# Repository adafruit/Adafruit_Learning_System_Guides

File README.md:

# Introduction

This is a collection of smaller programs and scripts to display "inline" in [Adafruit Learning System][learn] guides.

Adafruit is an Open Source company. To support Adafruit, please consider buying products at [adafruit.com](https://www.adafruit.com/).

Starting in 2023, guides using a specific Adafruit board will be placed in a subdirectory with that product name to reduce the number of directories under the main directory. If you are creating a new guide, please check if your Adafruit board falls into one of these groups and make your project code directory in the appropriate subfolder.

* Flora/
* ItsyBitsy/
* MagTag/
* MEMENTO/
* NeoTrellis/
* PyLeap/
* PyPortal/
* QTPy/
* Metro/ (all types)
* Matrix_Portal/
* Crickits/
* Gemma/ (both types)

If a new product or project group is contemplated, contact Learn moderators for guidance.

## Issues

Issues with guides should be reported in the guide itself under "Feedback? Corrections?"

## Make Your Own Guides

This repo is only for Adafruit approved Learning System Guides. If you'd like to write your own guide, see [Create your own content with Adafruit Playground!](https://learn.adafruit.com/adafruit-playground-notes).

## Contributing and Testing

For details on contributing for Adafruit approved guides, see the guide [Contribute to the Adafruit Learning System with Git and GitHub](https://learn.adafruit.com/contribute-to-the-adafruit-learning-system-with-git-and-github) and [Contribute to CircuitPython with Git and GitHub](https://learn.adafruit.com/contribute-to-circuitpython-with-git-and-github/github-personal-access-token).

The code here is checked by GitHub Actions against Pylint (for CircuitPython code) or the Arduino compilation process.

Code in directories containing a file called `.circuitpython.skip` will be skipped by Pylint checks.

Code in directories containing a `.[platformname].test` file, such as `.uno.test` will be compiled against the corresponding platform.

[learn]: https://learn.adafruit.com/

## Running pylint locally
Install a specific version of pylint under the name "pylint-learn":
```
pip install pipx
pipx install --suffix=-learn pylint==2.7.1
```
Then use the `pylint_check` script to run pylint on the files or directories
of your choice (note that your terminal *must* be in the top directory of
Adafruit_Learning_System_Guides, not a sub-directory):
```
./pylint_check CircuitPython_Cool_Project
```
## Licensing

Adafruit Learning System code files should have author and license information conforming to the open [SPDX specification](https://www.iso.org/standard/81870.html).
See [this page](https://learn.adafruit.com/contribute-to-the-adafruit-learning-system-with-git-and-github/add-author-and-license-information) for more.

Updated November 18, 2025

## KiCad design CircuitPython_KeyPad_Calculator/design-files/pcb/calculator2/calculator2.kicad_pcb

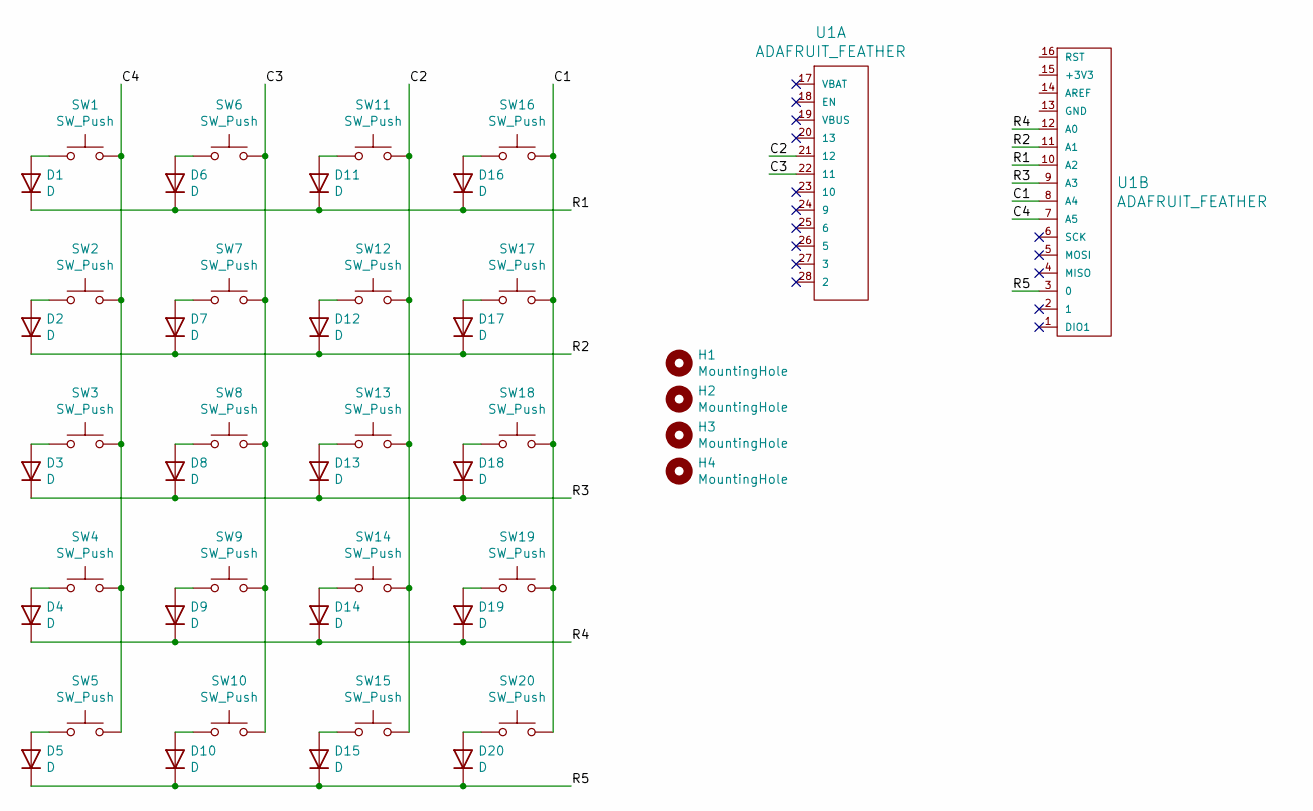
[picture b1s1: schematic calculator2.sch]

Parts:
D1, D2, D3, D4, D5, D6, D7, D8, D9, D10, D11, D12, D13, D14, D15, D16, D17, D18, D19, D20: D; D_DO-41_SOD81_P10.16mm_Horizontal
H1, H2, H3, H4: MountingHole; MountingHole_2.7mm_M2.5
SW1, SW2, SW3, SW4, SW5, SW6, SW7, SW8, SW9, SW10, SW11, SW12, SW13, SW14, SW15, SW16, SW17, SW18, SW19, SW20: SW_Push; SW_Cherry_MX_1.00u_PCB
U1: ADAFRUIT_FEATHER

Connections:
/C1: SW16.2, SW17.2, SW18.2, SW19.2, SW20.2, U1.8 (A4)
/C2: SW11.2, SW12.2, SW13.2, SW14.2, SW15.2, U1.21 (12)
/C3: SW6.2, SW7.2, SW8.2, SW9.2, SW10.2, U1.22 (11)
/C4: SW1.2, SW2.2, SW3.2, SW4.2, SW5.2, U1.7 (A5)
/R1: D1.1 (K), D6.1 (K), D11.1 (K), D16.1 (K), U1.10 (A2)
/R2: D2.1 (K), D7.1 (K), D12.1 (K), D17.1 (K), U1.11 (A1)
/R3: D3.1 (K), D8.1 (K), D13.1 (K), D18.1 (K), U1.9 (A3)
/R4: D4.1 (K), D9.1 (K), D14.1 (K), D19.1 (K), U1.12 (A0)
/R5: D5.1 (K), D10.1 (K), D15.1 (K), D20.1 (K), U1.3 (0)
unnamed: D1.2 (A), SW1.1
unnamed: D2.2 (A), SW2.1
unnamed: D3.2 (A), SW3.1
unnamed: D4.2 (A), SW4.1
unnamed: D5.2 (A), SW5.1
unnamed: D6.2 (A), SW6.1
unnamed: D7.2 (A), SW7.1
unnamed: D8.2 (A), SW8.1
unnamed: D9.2 (A), SW9.1
unnamed: D10.2 (A), SW10.1
unnamed: D11.2 (A), SW11.1
unnamed: D12.2 (A), SW12.1
unnamed: D13.2 (A), SW13.1
unnamed: D14.2 (A), SW14.1
unnamed: D15.2 (A), SW15.1
unnamed: D16.2 (A), SW16.1
unnamed: D17.2 (A), SW17.1
unnamed: D18.2 (A), SW18.1
unnamed: D19.2 (A), SW19.1
unnamed: D20.2 (A), SW20.1

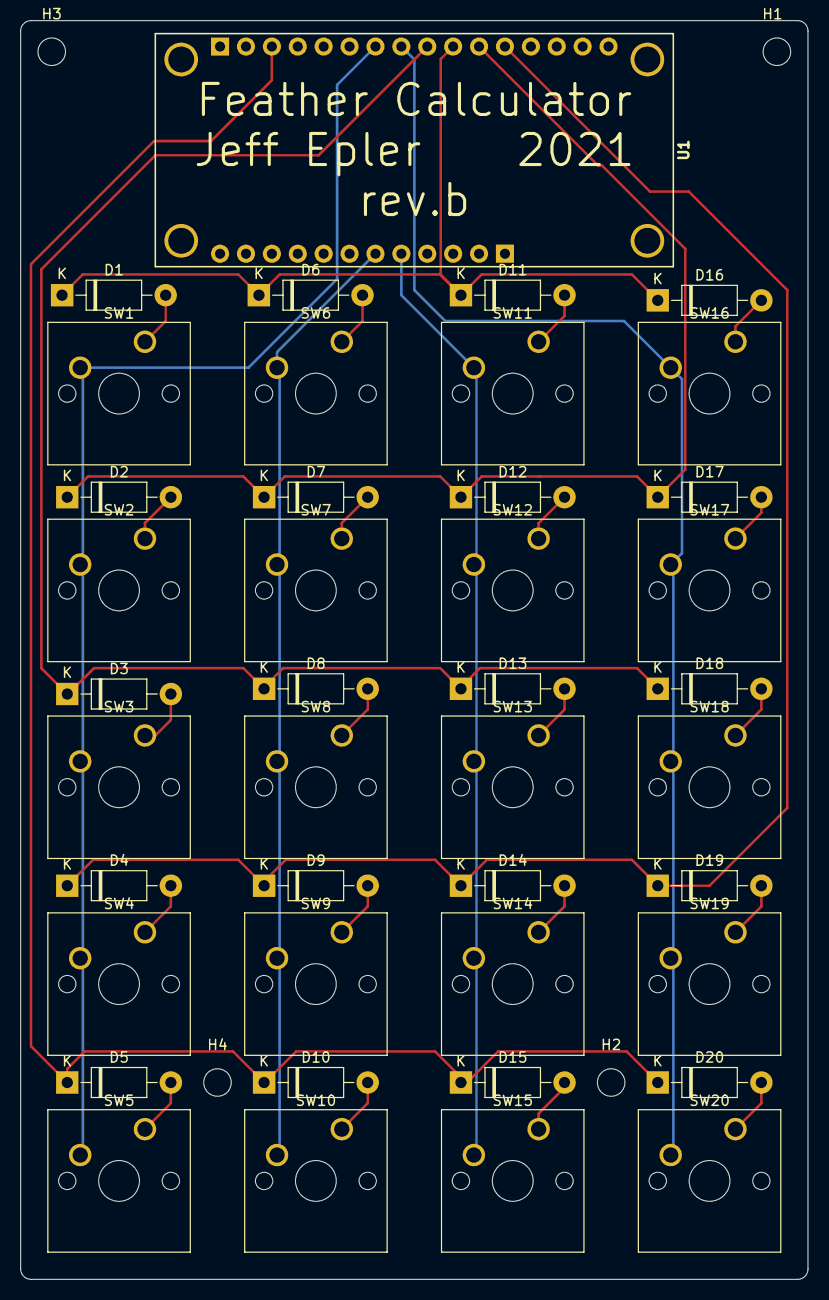
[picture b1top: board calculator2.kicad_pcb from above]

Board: 2 copper layers, 77.2 x 123.4 mm, 45 parts (0 on the bottom side), 29 nets.

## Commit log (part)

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2025-12-09 Format code for consistency in code.py
2025-12-09 Delete NeoPixel_Gemma_Torch directory
    Code moved to https://github.com/adafruit/Adafruit_Learning_System_Guides/tree/main/Gemma/NeoPixel_Gemma_Torch
    Guide updated https://learn.adafruit.com/neopixel-flame-torch/code
2025-12-10 literature clock data files and book info tweak
2025-12-11 fruit jam logo
2025-12-11 png fruit jam logo
2025-12-13 update images
2025-12-15 Clone Introducing Gemma to Gemma/
    For guide changes
2025-12-15 Delete Introducing_Gemma_M0 directory
    Files moved to Gemma/
    Adafruit Introducing Germma M0 updated (1 file, most examples used CircuitPython Essentials examples)
2025-12-17 adding magtag menorah code and bitmap
2025-12-18 Fruit Jam greeting card maker
2025-12-18 add/expand comments about each code file
2025-12-18 add checkbox spritesheet
2026-01-11 CircuitPython Text Editor 2.4" FeatherWing
2026-01-21 Add support for Composite HID devices
2026-01-21 move atexit import up one to make pylint happy
2026-01-21 first commit epaper cam code
2026-01-21 magtag haiku viewer project files
2026-01-22 Update code.py JSON_URL
    There was a change to the folder structure at some point and the MagTag projects were moved inside a MagTag folder and this URL was broken. Corrected to reflect the new URL and tested on my device.
2026-01-22 move haiku loading code, add font file
2026-01-23 Fix Eink bonnet weather station for PIL >= 10
2026-01-26 code and example mp3s
2026-01-26 use PCF font instead of BDF
2026-01-27 update folder name
2026-01-27 adding bass synth code
2026-01-28 take out readonly
    causing problems with stability, filed issue on cp repo
2026-02-10 adding midi breath controller code
2026-02-10 reduced lag in joystick code
2026-02-11 Fix display brightness scaling during fade down
    Adjust brightness scaling for display fade effect, same as fade up, noted in guide feedback
2026-02-13 pylint warning for chip's challenge
2026-02-13 Fruit Jam Tiny Wiki server
2026-02-13 rename storage -> wiki_storage, reduce long lines, change title note on new page, use f-string instead of format, ignore some pylints
2026-02-13 move _escape_html() out of class to normal function.
2026-02-13 fix tiny_wiki typo
2026-02-16 Updating cpb glass lamp code
    Putting the CPB glass lamp code in a directory for learn.
2026-02-17 fixed SPDX error
2026-02-17 Update SPDX license and copyright information
2026-02-20 Disable discovery options in feather_bme280.yaml
    Avoid unauthorised fixed topics like esphome/ping/{device-name}
2026-02-20 adding rpi moonshine voice control neopixels
2026-02-20 add license, code format, add link to original code this was adapted from.
2026-02-21 Replace worldtimeapi.org with time.now/developer API
    Updates 16 files to replace the deprecated worldtimeapi.org time
    service with the new time.now/developer API endpoint.
    ⏺ | Guide | Filename | Change URL |
    |-------|----------|------------|
    | PicoW_YBox3 | PicoW_YBox3.ino |
    `https://time.now/developer/api/timezone/Etc/UTC` |
2026-02-23 fix --model-arch CLI arg
2026-02-23 remove unused generic callback
2026-02-24 update for BitmapLabel color_palette argument handling
2026-02-27 PyPortal Art Display
    IoT-connected art gallery that cycles through art, space, cats and dogs! Pull from image feeds or images from an SD card. Skip images with a tilt or shake. Tap the screen to change feeds. Customize y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
2026-02-27 PyPortal Art Display
    Removed consider-using-f-string — that check was added in pylint 2.8, so 2.7.1 doesn't recognize it and throws bad-option-value (exit code 123 even with a 10/10 score). Since 2.7.1 won't flag the %-f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
2026-02-27 Added code.py to it's own folder
    Added the folder PyPortal_Art_Display and put the code.py file in it.
2026-02-27 Refactored code.py
    Refactored code rather than blanket-disables
2026-02-27 global variable naming fix code.py
    adding invalid-name to each # pylint: disable=global-statement line catches it where it actually fires. All 10 global lines now have both disables.
2026-03-02 update arduino examples for 2025 magtag
2026-03-10 Update color constants to RGB565 format
2026-03-10 Update color constants to use RGB565 format
2026-03-11 Add initial implementation of camera control script
2026-03-11 Create settings.toml with initial configuration
    Add configuration settings for WiFi, API key, timezone, and AI prompt.
2026-03-11 Rename code.py to code.py
2026-03-11 Rename MEMENTO/Mementoflex/projectfiles/settings.toml to MEMENTO/Mementoflex/settings.toml
2026-03-14 adding 4.58" 320x960 rectangle bar display
    current qualia factory demo code was missing 4.58" 320x960 ADA# 5805 init / pulse / sync.
2026-03-16 code for blurry matrix clock
    analog clock with hour and minute hands over a
    gradient background that shifts through four palettes across
    the day.
2026-03-18 adding xteink x4 demos
    weather demo and bitmap display demo
2026-03-18 fix fstring
2026-03-19 Updating workflows to use actions using Node 24
2026-03-21 MagTag Daily Weather: Add battery state display
    Curious as to how long it's lasting, figured
    daily updates on battery state would be good.
    Also print battery state on the console.
2026-03-21 Fix missed renaming
2026-03-21 Fix extraneous import
2026-03-24 Adding code for midi neopixel visualizer
    code for the midi neopixel visualizer
2026-03-24 fix for pylint
    updating code to fix for pylint
2026-03-24 add simple arduino demo for ADS122C04
2026-03-30 adding fruit jam egg hunt maze game
2026-03-30 Create code.py
    Star Trek TNG Data Dispenser Prop - Environmental Monitor.
    Displays CO2, humidity, temperature and battery level as
    shaped colored bars on the ESP32-S3 Reverse TFT Feather
2026-03-30 Update code.py
    Six fixes for the CI failures
2026-03-31 refactor fixes to code.py
    @BlitzCityDIY excellent Claude updated and saved skills to memory:
    Updated:
    #1 — Expanded CI rules with exit code 123 behavior, full file-level disable list, inline disable thresholds, f-string requirement
    New:
    #8 — Code review patterns (STEMMA_I2C, imports at top, no defensive wrapping of required sensors, consolidate functions)
    #9 — ESP32-S3 Reverse TFT hardware gotchas (CP 9.2.9, TFT_I2C_POWER, D0/BOOT0 PinAlarm false triggers, light sleep workaround)
2026-03-31 pylint disables, Debouncer and import fixes
    excellent thanks @BlitzCityDIY @TheKitty
    here are the round of adjustments:
    1. f-string syntax error (line 2009)
    Extracted conditional to zoom_label variable
    2. DRV2605 shouldn't be optional import
    Moved to normal import adafruit_drv2605 at top
2026-03-31 f-string fix
    f-string fix No more instances left in the file
2026-03-31 too-many-branches fix
    Added too-many-branches to the existing inline disable on _update_lcars_graph
2026-04-01 Add README for fonts in version 2
2026-04-01 Fix ppylint errors
2026-04-01 Fix one scope issue not caught previously
2026-04-01 add import and init for pre-2024 bonnet
2026-04-07 update circuitpython dvi sock demo
    received guide feedback that this example throws a memoryerror with current circuitpython on the original pico. updated to only run some of the examples for the rp2040 pico, while still running all o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
2026-04-08 first commit Onekey sketch and web page
2026-04-08 moved ino file out of dir
2026-04-10 Swap I2SOut pins for audio output
    Call I2SOut with correct pin order
2026-04-13 add code for esp-now walkie talkies
2026-04-16 added licensing info
2026-04-16 added corrected license info
2026-04-20 adding tetris mit green building code
2026-04-21 add font file for tetris
2026-04-24 matrixportal world cup code and graphics
2026-04-24 ran older version of pylint locally, fixed errors
2026-04-26 arduino_cron.yml: fix
2026-04-26 arduino_cron.yml: check-upated 'if:' is not needed
2026-04-30 Create code.py
    Initial commit
2026-04-30 Update code.py
    Fixed pylint issues.
2026-04-30 Update code.py
    Added missing final newline
2026-05-05 adding Sensor_Locked_Secrets
2026-05-05 fix gps typo
2026-05-05 fix licenses
2026-05-07 clue ble beacon
    clue ble remote code
2026-05-07 BLE beacon ears
    QTPy code to make into a BLE receiver
2026-05-07 Update code.py
    Removed unused import neopixel line
    32339 bytes (16 bytes smaller, slightly more headroom under the cliff)
    Lint clean even with unused-import enforced (Adafruit CI doesn't disable that one — my local config did, mistake on my part)
    Behavior unchanged — neopixel was never actually used here, only inside pixel_zones.py
2026-05-09 fixes to code, main and added battery.py
    applied fixes to code, removed main and added battery.py
2026-05-09 code.py format fixes
    formatting issue fixes in code.py
2026-05-13 first commit cluetooth code
2026-05-13 fix pylint error
2026-05-16 Changed order of NeoPixel lighting
    NeoPixel currently holds on to cyan or pink color after the connection test, instead of indicating water level in the test. I moved the NeoPixel color display down, so that the water level status col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
2026-05-21 add embodiment kit files
2026-05-21 fix remaining spdx headers
2026-05-21 refactor methods to functions. pylint disable for too large functions in CLI script
2026-05-21 remove broad except, black format CLI script
2026-05-28 prop it game code
    adding code for prop it game
2026-05-28 lint
2026-06-08 adding final code and sfx files
2026-06-08 line too long
2026-06-12 Pi video feedback project
2026-06-14 Minecraft code
    code for the minecraft gps compass
2026-06-18 Do not ignore RuntimeError when doing pin finding
2026-06-21 minecraft GPS compass code
    minecraft GPS compass code
2026-06-22 code fixes
    1. MAX17048 wrapped in try/except
    2. Blocking time.sleep in the loop — replaced the blocking message flashes with a non-blocking flash-message system
    3. adafruit_debouncer.Button (mc_compass) — replaced my hand-rolled two-tier hold timing
    4. recalibration no longer deletes the whole file. It now rewrites settings.toml keeping every non-MAG_ line, clearing only the calibration keys this project owns.
2026-06-23 adding code for circuitpython chiptune player
2026-06-23 add header comment
2026-06-24 Fix for hold-to-save
    Fix hold-to-save: time the hold from the debounced level, not edge flags
    The Button.pressed/released one-shot edge flags intermittently dropped a
    press, so hold-to-save would fall through and register as a short tap
    (switching mode instead of saving). poll_button now reads the debounced
    level (button.value) and detects the press/release edges itself, timing
    the hold with time.monotonic(). This also survives the ~300-500 ms loop
2026-06-24 Set file mode to 100644 (remove executable bit)
2026-06-24 CPB Morse code paddle project code
2026-06-24 use keypad instead of adafruit_debouncer, change paddle to key
